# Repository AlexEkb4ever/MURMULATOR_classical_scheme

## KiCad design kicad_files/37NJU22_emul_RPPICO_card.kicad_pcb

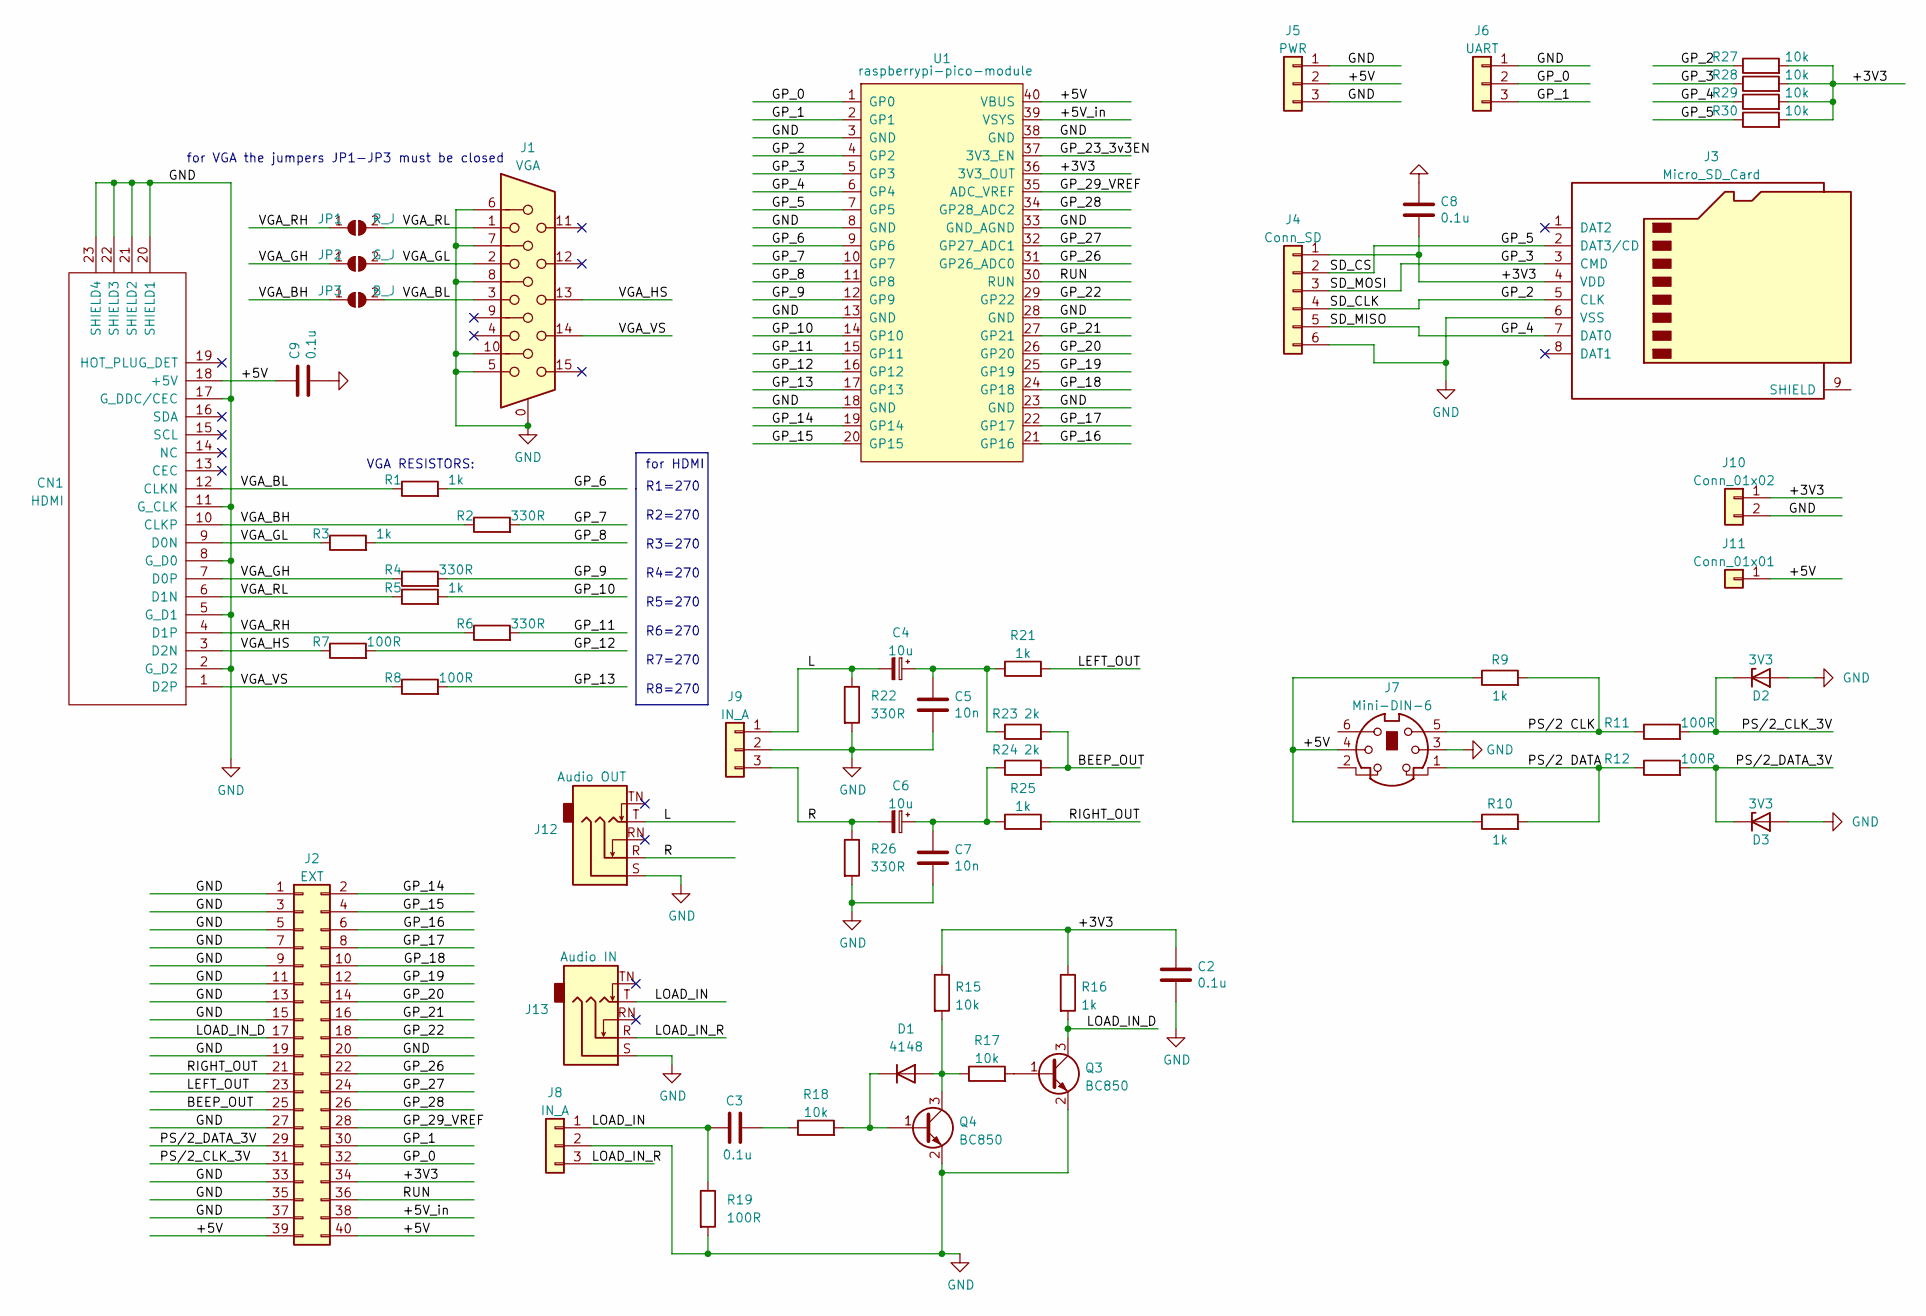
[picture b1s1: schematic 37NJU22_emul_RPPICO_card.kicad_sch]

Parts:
C2, C3, C8, C9: 0.1u; R_0805_PLUS
C4, C6: 10u; CP_Radial_D5.0mm_P2.50mm
C5, C7: 10n; R_0805_PLUS
CN1: HDMI
D1: 4148; R_0805_PLUS
D2, D3: 3V3; D_1206_3216Metric
J1: VGA; DSUB-15-HD_Female_Horizontal_P2.29x1.98mm_EdgePinOffset3.03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
J2: EXT; PinHeader_2x20_P2.54mm_Vertical
J3: Micro_SD_Card; GCT-MEM2055-00-190-01-A
J4: Conn_SD; PinSocket_1x06_P2.54mm_Vertical
J5: PWR; PinHeader_1x03_P2.54mm_Vertical
J6: UART; PinHeader_1x03_P2.54mm_Vertical
J7: Mini-DIN-6; Connector_Mini-DIN_Female_6Pin_2rows
J8, J9: IN_A; PinHeader_1x03_P2.54mm_Vertical
J10: Conn_01x02; PinHeader_1x02_P2.54mm_Vertical
J11: Conn_01x01; PinHeader_1x01_P2.54mm_Vertical
J12: Audio OUT; Jack_3.5mm_CUI_SJ1-3535NG_Horizontal
J13: Audio IN; Jack_3.5mm_CUI_SJ1-3535NG_Horizontal
JP1: R_J; SolderJumper-2_P1.3mm_Open_RoundedPad1.0x1.5mm
JP2: G_J; SolderJumper-2_P1.3mm_Open_RoundedPad1.0x1.5mm
JP3: B_J; SolderJumper-2_P1.3mm_Open_RoundedPad1.0x1.5mm
Q3, Q4: BC850; SOT-23_PLUS
R1, R3, R5, R9, R10, R16, R21, R25: 1k; R_0805_PLUS
R2, R4, R6, R22, R26: 330R; R_0805_PLUS
R7, R8, R11, R12, R19: 100R; R_0805_PLUS
R15, R18: 10k; R_0805_PLUS
R17: 10k; R_0805_2012Metric
R23, R24: 2k; R_0805_PLUS
R27, R28, R29, R30: 10k; R_0805_2012Metric_Pad1.20x1.40mm_HandSolder
U1: raspberrypi-pico-module; Raspberry_Pi_Pico_SMT_THT_MOD_2

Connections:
/+3V3: C2.1, C8.2, J2.34, J3.4 (VDD), J4.1, J10.1, R15.1, R16.1, R27.2, R28.2, R29.2, R30.2, U1.36 (3V3_OUT)
/+5V: C9.1, CN1.18 (+5V), J2.39, J2.40, J5.2, J7.4, J11.1, R9.1, R10.1, U1.40 (VBUS)
/+5V_in: J2.38, U1.39 (VSYS)
/BEEP_OUT: J2.25, R23.2, R24.2
/GP_0: J2.32, J6.2, U1.1 (GP0)
/GP_1: J2.30, J6.3, U1.2 (GP1)
/GP_2: J3.5 (CLK), J4.4, R27.1, U1.4 (GP2)
/GP_3: J3.3 (CMD), J4.3, R28.1, U1.5 (GP3)
/GP_4: J3.7 (DAT0), J4.5, R29.1, U1.6 (GP4)
/GP_5: J3.2 (DAT3/CD), J4.2, R30.1, U1.7 (GP5)
/GP_6: R1.2, U1.9 (GP6)
/GP_7: R2.2, U1.10 (GP7)
/GP_8: R3.2, U1.11 (GP8)
/GP_9: R4.2, U1.12 (GP9)
/GP_10: R5.2, U1.14 (GP10)
/GP_11: R6.2, U1.15 (GP11)
/GP_12: R7.2, U1.16 (GP12)
/GP_13: R8.2, U1.17 (GP13)
/GP_14: J2.2, U1.19 (GP14)
/GP_15: J2.4, U1.20 (GP15)
/GP_16: J2.6, U1.21 (GP16)
/GP_17: J2.8, U1.22 (GP17)
/GP_18: J2.10, U1.24 (GP18)
/GP_19: J2.12, U1.25 (GP19)
/GP_20: J2.14, U1.26 (GP20)
/GP_21: J2.16, U1.27 (GP21)
/GP_22: J2.18, U1.29 (GP22)
/GP_23_3v3EN: U1.37 (3V3_EN)
/GP_26: J2.22, U1.31 (GP26_ADC0)
/GP_27: J2.24, U1.32 (GP27_ADC1)
/GP_28: J2.26, U1.34 (GP28_ADC2)
/GP_29_VREF: J2.28, U1.35 (ADC_VREF)
/L: C4.2, J9.1, J12.T, R22.1
/LEFT_OUT: J2.23, R21.2
/LOAD_IN: C3.1, J8.1, J13.T, R19.1
/LOAD_IN_D: J2.17, Q3.3 (C), R16.2
/LOAD_IN_R: J8.3, J13.R
/PS/2 CLK: J7.5, R9.2, R11.1
/PS/2 DATA: J7.1, R10.2, R12.1
/PS/2_CLK_3V: D2.1 (K), J2.31, R11.2
/PS/2_DATA_3V: D3.1 (K), J2.29, R12.2
/R: C6.2, J9.3, J12.R, R26.1
/RIGHT_OUT: J2.21, R25.2
/RUN: J2.36, U1.30 (RUN)
/VGA_BH: CN1.10 (CLKP), JP3.1 (A), R2.1
/VGA_BL: CN1.12 (CLKN), J1.3, JP3.2 (B), R1.1
/VGA_GH: CN1.7 (D0P), JP2.1 (A), R4.1
/VGA_GL: CN1.9 (D0N), J1.2, JP2.2 (B), R3.1
/VGA_HS: CN1.3 (D2N), J1.13, R7.1
/VGA_RH: CN1.4 (D1P), JP1.1 (A), R6.1
/VGA_RL: CN1.6 (D1N), J1.1, JP1.2 (B), R5.1
/VGA_VS: CN1.1 (D2P), J1.14, R8.1
GND: C2.2, C5.2, C7.2, C8.1, C9.2, CN1.2 (G_D2), CN1.5 (G_D1), CN1.8 (G_D0), CN1.11 (G_CLK), CN1.17 (G_DDC/CEC), CN1.20 (SHIELD1), CN1.21 (SHIELD2), CN1.22 (SHIELD3), CN1.23 (SHIELD4), D2.2 (A), D3.2 (A), J1.0, J1.5, J1.6, J1.7, J1.8, J1.10, J2.1, J2.3, J2.5, J2.7, J2.9, J2.11, J2.13, J2.15, J2.19, J2.20, J2.27, J2.33, J2.35, J2.37, J3.6 (VSS), J4.6, J5.1, J5.3, J6.1, J7.3, J8.2, J9.2, J10.2, J12.S, J13.S, Q3.2 (E), Q4.2 (E), R19.2, R22.2, R26.2, U1.3 (GND), U1.8 (GND), U1.13 (GND), U1.18 (GND), U1.23 (GND), U1.28 (GND), U1.33 (GND_AGND), U1.38 (GND)
unnamed: C3.2, R18.1
unnamed: C4.1, C5.1, R21.1, R23.1
unnamed: C6.1, C7.1, R24.1, R25.1
unnamed: D1.1 (K), Q4.1 (B), R18.2
unnamed: D1.2 (A), Q4.3 (C), R15.2, R17.1
unnamed: Q3.1 (B), R17.2

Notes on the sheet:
for VGA the jumpers JP1-JP3 must be closed
VGA RESISTORS:
for HDMI
R1=270 R2=270 R3=270 R4=270 R5=270 R6=270 R7=270 R8=270

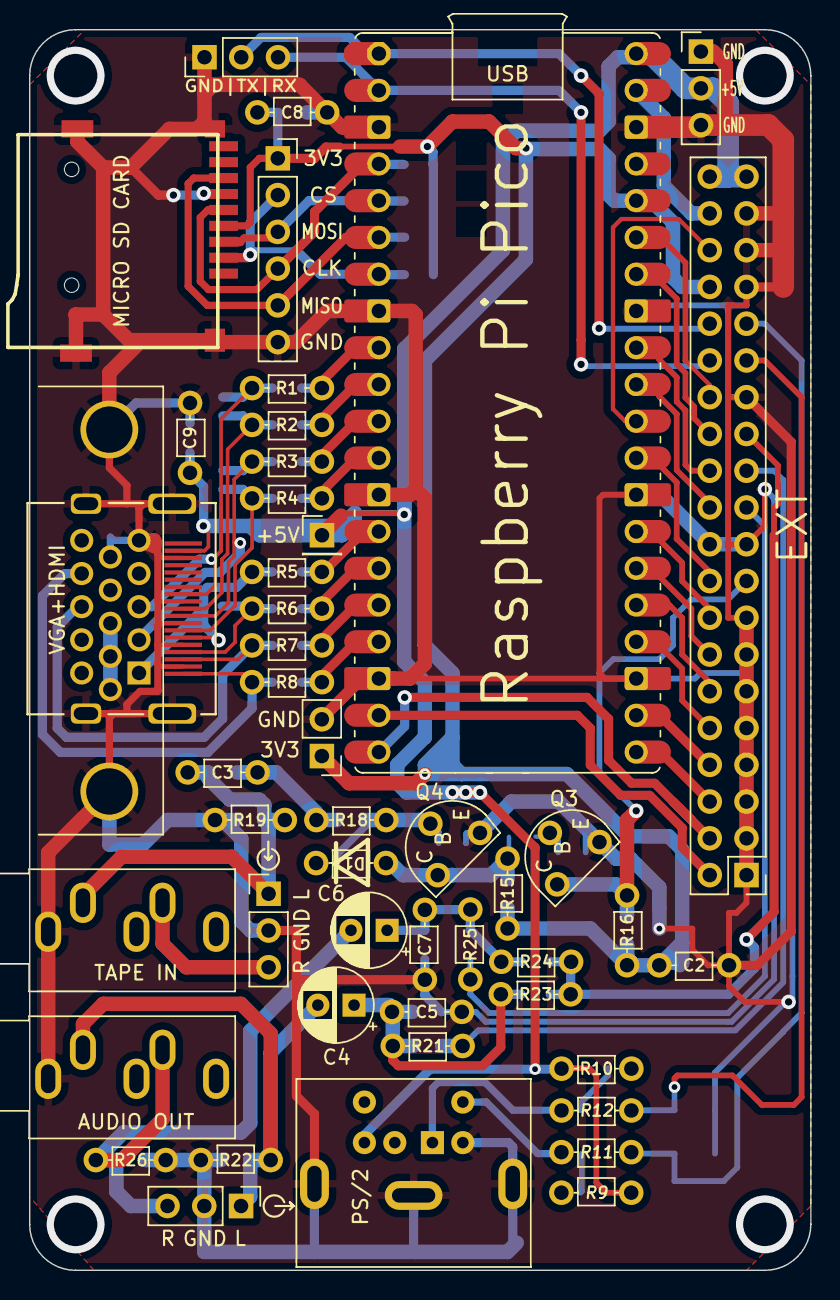
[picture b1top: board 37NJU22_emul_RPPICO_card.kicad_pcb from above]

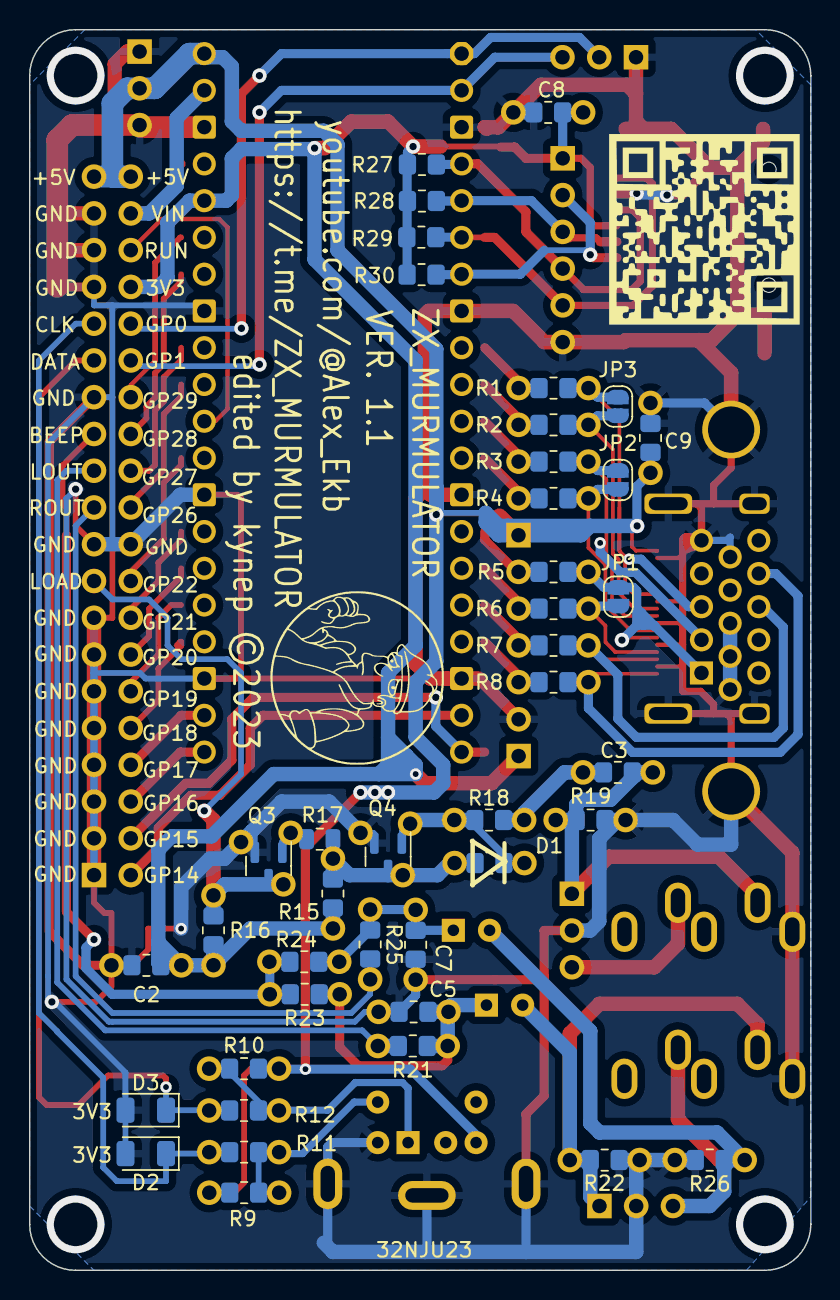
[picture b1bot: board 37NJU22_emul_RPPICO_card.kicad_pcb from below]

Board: 2 copper layers, 54.0 x 85.7 mm, 58 parts (41 on the bottom side), 58 nets.

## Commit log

2023-08-11 create

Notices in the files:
kicad_files/37NJU22_emul_RPPICO_card.kicad_pcb:
edited by kynep ©2023
